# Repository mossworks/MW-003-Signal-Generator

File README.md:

# MW-003-Signal-Generator
Takes 6-36VDC input and generates a selectable 0-10VDC or 0-20mA output (the actual range can be adjusted using the trim pot on the - input of the op-amp).

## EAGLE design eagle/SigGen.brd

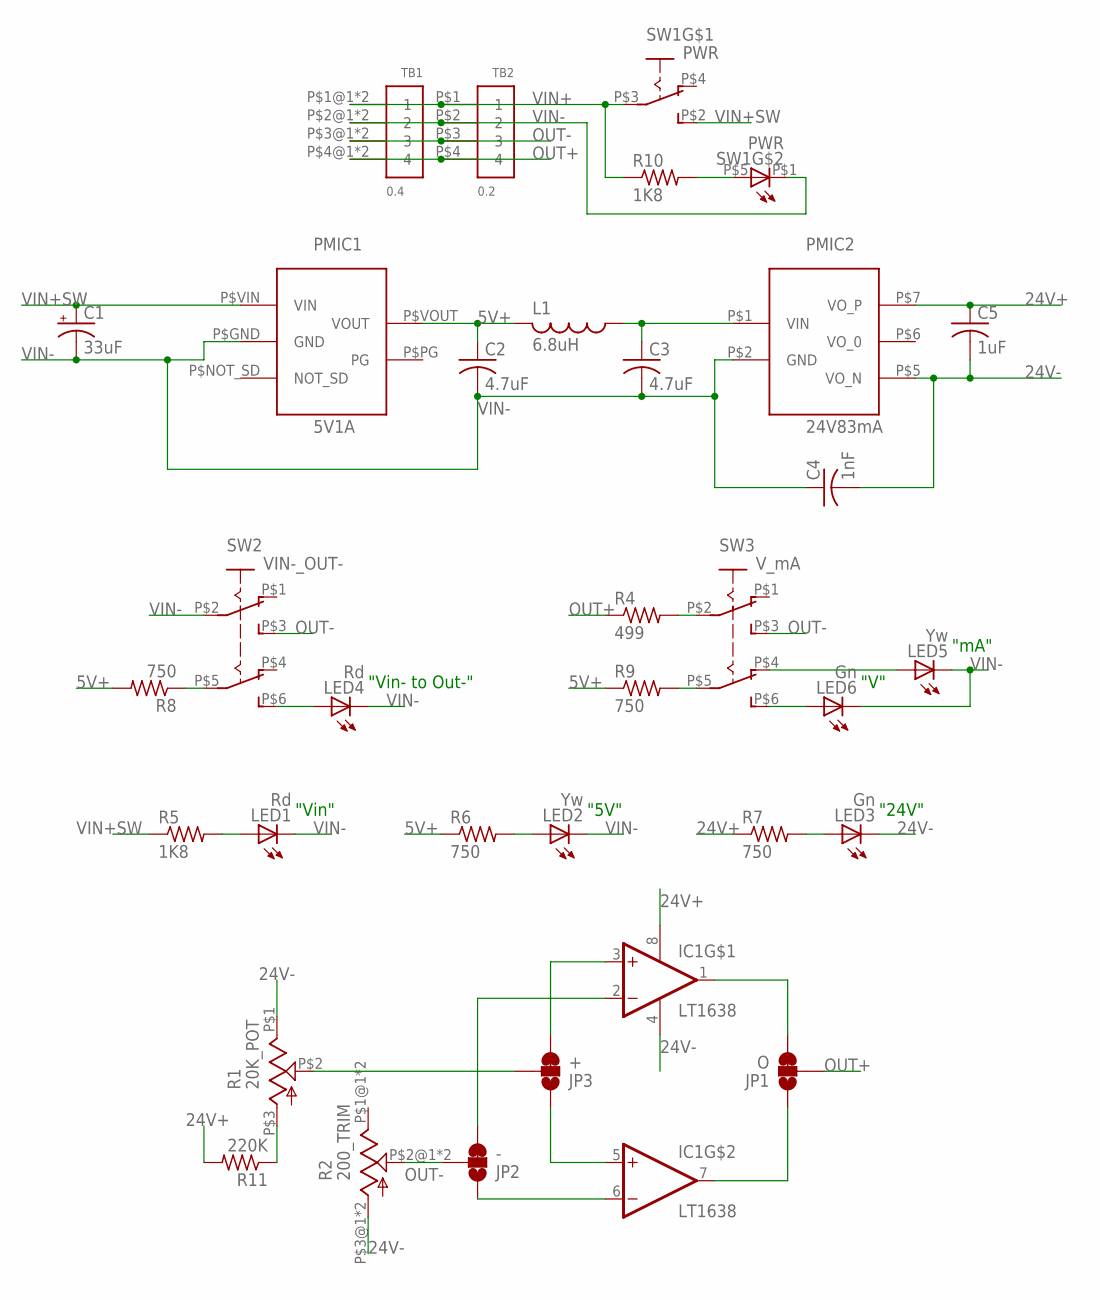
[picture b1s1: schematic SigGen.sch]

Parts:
C1: 33uF; CAP_0.315D
C2, C3: 4.7uF; C025-024X044
C4: 1nF; C075-032X103
C5: 1uF; C050-024X044
IC1: LT1638; DIP8
JP1: O; SMT-JUMPER_3_1-NC_TRACE_NO-SILK
JP2: -; SMT-JUMPER_3_1-NC_TRACE_NO-SILK
JP3: +; SMT-JUMPER_3_1-NC_TRACE_NO-SILK
L1: 6.8uH; IND_0.197D
LED1, LED4: Rd; LED3MM
LED2, LED5: Yw; LED3MM
LED3, LED6: Gn; LED3MM
PMIC1: 5V1A; PMIC_POLOLU-5X7
PMIC2: 24V83mA; PMIC_PEM2-S
R1: 20K_POT; POT_PDB181-K
R2: 200_TRIM; POT_89
R4: 499; 0204/7
R5, R10: 1K8; 0204/7
R6, R7, R8, R9: 750; 0204/7
R11: 220K; 0204/7
SW1: PWR; ELUM_SWITCH_TH_ILLUMINATED
SW2: VIN-_OUT-; SW_TL2201
SW3: V_mA; SW_TL2201
TB1: 0.4; 1X04_LARGE_10.16MM
TB2: 0.2; 1X04_LARGE_5.08MM

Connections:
5V+: C2.1, L1.P$2 (2), PMIC1.P$VOUT (VOUT), R6.1, R8.2, R9.1
24V+: C5.1, IC1.8 (V+), PMIC2.P$7 (VO_P), R7.1, R11.2
24V-: C4.2, C5.2, IC1.4 (V-), LED3.K (C), PMIC2.P$5 (VO_N), R1.P$1 (CCW), R2.P$3@1 (CW), R2.P$3@2 (CW)
unnamed: LED1.A, R5.2
unnamed: C3.1, L1.P$1 (1), PMIC2.P$1 (VIN)
unnamed: R8.1, SW2.P$5 (COM2)
unnamed: LED2.A, R6.2
unnamed: LED3.A, R7.2
unnamed: R4.2, SW3.P$2 (COM1)
unnamed: LED4.A, SW2.P$6 (NO2)
unnamed: R9.2, SW3.P$5 (COM2)
unnamed: LED6.A, SW3.P$6 (NO2)
unnamed: LED5.A, SW3.P$4 (NC2)
unnamed: R1.P$3 (CW), R11.1
unnamed: JP3.2, R1.P$2 (WIPER)
unnamed: IC1.7 (OUT), JP1.1
unnamed: R10.2, SW1.P$5 (A)
unnamed: IC1.1 (OUT), JP1.3
unnamed: IC1.3 (+IN), JP3.3
unnamed: IC1.5 (+IN), JP3.1
unnamed: IC1.2 (-IN), JP2.3
unnamed: IC1.6 (-IN), JP2.1
OUT+: JP1.2, R4.1, TB1.P$4@1 (4), TB1.P$4@2 (4), TB2.P$4 (4)
OUT-: JP2.2, R2.P$2@1 (WIPER), R2.P$2@2 (WIPER), SW2.P$3 (NO1), SW3.P$3 (NO1), TB1.P$3@1 (3), TB1.P$3@2 (3), TB2.P$3 (3)
VIN+: R10.1, SW1.P$3 (COM), TB1.P$1@1 (1), TB1.P$1@2 (1), TB2.P$1 (1)
VIN+SW: C1.P$2_POS (+), PMIC1.P$VIN (VIN), R5.1, SW1.P$2 (NO)
VIN-: C1.P$1_NEG (-), C2.2, C3.2, C4.1, LED1.K (C), LED2.K (C), LED4.K (C), LED5.K (C), LED6.K (C), PMIC1.P$GND (GND), PMIC2.P$2 (GND), SW1.P$1 (C), SW2.P$2 (COM1), TB1.P$2@1 (2), TB1.P$2@2 (2), TB2.P$2 (2)

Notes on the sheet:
"Vin"
"5V"
"24V"
"Vin- to Out-"
"V"
"mA"

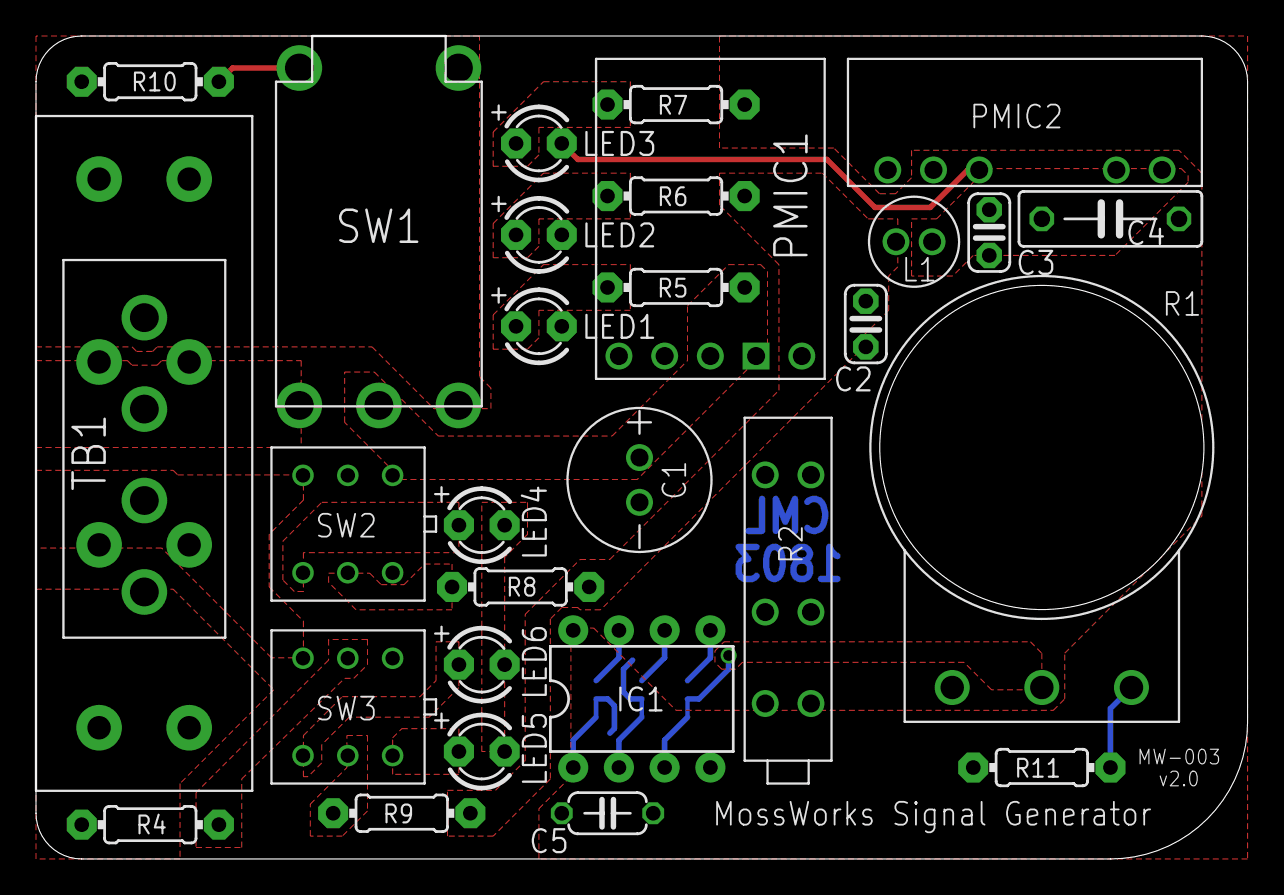
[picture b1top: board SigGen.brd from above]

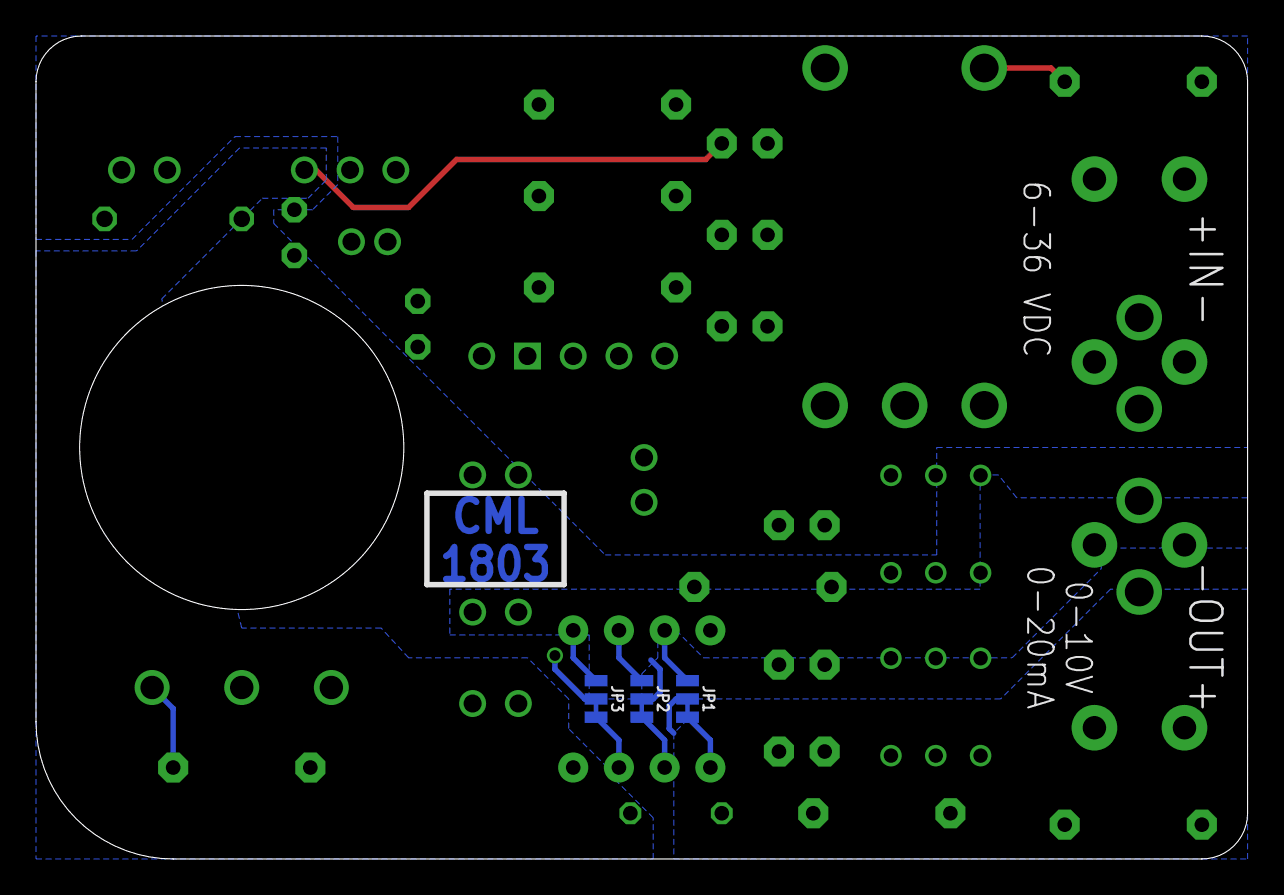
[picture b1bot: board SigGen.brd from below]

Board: 2 copper layers, 67.3 x 45.7 mm, 33 parts (3 on the bottom side), 27 nets.

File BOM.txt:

TB1 - 0.4" pitch terminal block (Digikey 732-11097-ND)
TB2 - 0.2" pitch terminal block (Digikey 609-3938-ND)
(Choose one terminal block or the other, not both)
SW1 - Illuminated push-on, push-off switch (Digikey CKN9038-ND)
SW2, SW3 - DPDT push-on, push-off switch (Digikey EG5461-ND)
IC1 - Op-amp (Digikey LT1638CN8#PBF-ND)
PMIC1 - 5V buck regulator (Pololu D24V10F5)
PMIC2 - 24V boost regulator (Digikey 102-3045-5-ND)
L1 - 6.8uH inductor (Digikey 811-2023-ND)
C1 - 33uF electrolytic capacitor (Digikey P838-ND)
C2, C3 - 4.7uF ceramic capacitor (Digikey 445-173131-1-ND)
C4 - 1nF 3000V ceramic capacitor (Digikey 1253PH-ND)
C5 - 1uF ceramic capacitor (Digikey 490-8911-ND)
R1 - 20K potentiometer, leads must be bent down (Digikey PDB181-K420K-203B-ND)
R2 - 200R trim potentiometer (Digikey 987-1560-ND)
R4 - 499R precision resistor (converts 0-20mA to 0-10V.  Use 249R for 0-5V, etc)
R5, R10 - 1K8 resistor
R6, R7, R8, R9 - 750R resistor
R11 - 220K resistor
LED1, LED4 - Red T-1 LED
LED2, LED5 - Yellow T-1 LED
LED3, LED6 - Green T-1 LED

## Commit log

2018-03-12 Eagle Files
    Eagle .brd and .sch files
2018-03-12 Initial version

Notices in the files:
parts and their libraries:
SparkFun-Jumpers: Licensing: Creative Commons ShareAlike 4.0 International - https://creativecommons.org/licenses/by-sa/4.0
